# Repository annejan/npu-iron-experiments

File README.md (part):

# IRON experiments on a Ryzen AI NPU

One night (7 November 2026) of finding out what the NPU in an AMD Ryzen AI 7 PRO 350 laptop
(a ThinkPad; XDNA2, AMD codename Krackan Point, `xrt-smi` calls it "NPU Krackan") is good at,
programmed directly in IRON, the Python front end of AMD/Xilinx [mlir-aie](https://github.com/Xilinx/mlir-aie)
1.4.5, under Linux (openSUSE Tumbleweed, kernel 7.3 with the in-tree `amdxdna` driver). Demoscene
effects, physics simulations, audio DSP and one real object detector, each checked against numpy
and timed; plus the probes that measured the chip's ceilings, and every trap hit on the way.

Most of the code was written by [Claude Code](https://claude.com/claude-code) (Anthropic's agent)
working with Anne Jan Brouwer over one evening and night; every commit carries a `Co-Authored-By`
trailer saying so. All numbers are measurements on this one laptop, not AMD specifications, unless
a line says otherwise. See "Credits and licences" at the end for what is borrowed from whom.

Short version: the chip is 32 small vector cores with 64 KB each, fed by fast DMA. It shines on
anything branchless and MAC-shaped where every lane does the same work: stencils, convolutions,
FIR audio, int8 matrix multiplies, lookup tables. It is poor at gathers, trig, fp32 multiplies and
anything that needs a big table. A dispatch costs ~160 us before any work, so batch work per call.

## Setup

Hardware and kernel: a Ryzen AI 300 NPU (Strix Point, Krackan Point or Strix Halo; PCI `1022:17f0`),
Linux 6.14 or newer with the in-tree `amdxdna` driver (`CONFIG_DRM_ACCEL_AMDXDNA`) and the `amdnpu`
firmware (Tumbleweed: `kernel-default` + `kernel-firmware-platform`). `/dev/accel/accel0` is owned by
`root:render`, so add yourself to the `render` group. `lsmod | grep amdxdna` and `ls /lib/firmware/amdnpu`
tell you whether both are there.

XRT (AMD's runtime) is not in any distribution. This repo expects it unpacked, not installed, in
`../ryzenai` (nothing goes into `/opt`):

```
mkdir -p ../ryzenai/dl ../ryzenai/x && cd ../ryzenai
# into dl/: RAI_1.9_Linux_NPU_XRT.zip from AMD's "Ryzen AI Software 1.9, Linux" download page (AMD EULA), which holds
#   xrt_202620.2.26.89_24.04-amd64-{base,base-dev,npu}.deb and xrt_plugin.2.26.260102.59.release_24.04-amd64-amdxdna.deb,
# plus the two Ubuntu 24.04 packages the XRT binaries link against:
#   libboost-filesystem1.83.0_*.deb and libboost-program-options1.83.0_*.deb (packages.ubuntu.com)
for d in dl/*.deb; do dpkg-deb -x "$d" "x/$(basename "$d" .deb)"; done     # no dpkg? ar p X.deb data.tar.zst | tar -x --zstd
mkdir -p xrt boost
for p in x/xrt_*/opt/xilinx/xrt x/xrt_plugin*/opt/xilinx/xrt; do cp -a "$p/." xrt/; done
cp -a x/libboost*/usr boost/
```

`env.sh` points `XILINX_XRT`, `LD_LIBRARY_PATH` and `PYTHONPATH` (for `pyxrt`) at those two
directories. `pyxrt` is built for CPython 3.12 and the `mlir_aie` wheel is `cp312`, hence `python3.12`
in `setup.sh` (Tumbleweed: `zypper in python312`). Then, from this directory:

```
./setup.sh                      # clones mlir-aie v1.4.5 (no submodules), makes ironenv/ with mlir_aie 1.4.5,
                                # the pinned Peano (llvm-aie) compiler and the demo extras (~2 GB)
./env.sh xrt-smi examine        # the device: "NPU Krackan 1 | aie2p | 6x8"
```

## Quick start

```
./env.sh make -C mlir-aie/programming_examples/basic/vector_scalar_mul run_py   # smoke test, ends with PASS!
./env.sh python probe/plasma.py --window        # 1080p plasma in a pygame window
./env.sh python fun/mandel.py                   # Mandelbrot zoom in the terminal; --png out.png writes one frame
./env.sh python fun/lenia.py --window           # Lenia
./env.sh python fun/reverb.py --live            # microphone -> NPU convolution reverb -> headphones
```

Every command runs from this directory (the scripts find each other through `fun/` and `probe/`).
The first run of each design compiles its kernels (0.4-1.7 s, cached in `~/.npu/cache`,
`NPU_CACHE_HOME` overrides), and every `./env.sh` call runs `xrt-smi examine` once to find the device,
so starts take a moment. Run one NPU job at a time. `--window` needs pygame-ce; the audio demos need
soundfile and sounddevice, the live ones headphones.

## Pictures

| | | |
|---|---|---|
|  Lenia, 27x27 kernel |  Physarum network |  Schrodinger double slit |
|  Ising at Tc |  Lattice-Boltzmann vortex street |  Ripple tank |
|  SDF sphere tracer |  Smooth-min blobs |  Mandelbrot, 32 cores |
|  Abelian sandpile, 2^18 grains |  Gray-Scott coral |  YOLO26n, 150 fps, real weights |
|  Cyclic CA demons |  Greenberg-Hastings spirals |  1080p plasma, 0.34 ms/frame |
|  Corridor impulse response, 3-D FDTD |  Neural style transfer, 5 styles, 16.7 ms/frame |  The NPU learns MNIST, 50 ms/epoch |
|  Pong via a shortcut (see the section) | | |

(The YOLO and style pictures are COCO 2017 image 30: photo by julie, https://www.flickr.com/photos/roosterfarm/3573516590, CC BY 2.0, boxes added / restyled by the NPU.)

## Hardware (xrt-smi: "NPU Krackan 1", aie2p, 6x8)

| | |
|---|---|
| Compute cores | 32 (8 columns x rows 2..5), 1.76 GHz |
| Per core | 64 KB data memory (4 banks of 16 KB), 512-bit vector unit, 2 DMA in + 2 out |
| Mem tiles | 8 (row 1), 512 KB each |
| Shim tiles | 8 (row 0), 2 DMA channels each way, host DDR access |
| Vector lanes | 64 x int8, 32 x int16, 16 x int32, 32 x bf16 |
| Native math | int add/mul/mac/shift/cmp/select/shuffle, bf16 mul, `aie::inv`, `aie::invsqrt`, `aie::sqrt`, `aie::exp2`, `aie::tanh` (bf16) |
| Not native | float vector multiply (emulated via bf16, ~50 bundles/vector), scalar float mul/div, int32 divide, 64-bit multiply, sin/cos (use tables / polynomials), per-lane gather |

Sources: the name and the 6x8 array from `xrt-smi examine`; tile memories, DMA channels and lane
widths from the AIE-ML v2 (aie2p) architecture documentation and `mlir-aie/programming_guide/section-1`.
AMD does not publish the clock: ~1.76 GHz is what the II-1 loop in `probe/burn.py` implies, and
`probe/npu_top.py` reads the driver's H clock. "Native" means Peano compiles it to vector
instructions rather than a library call.

## Measured ceilings (2026-11-07, `probe/`)

All numbers: this one laptop, Linux, XRT 2.26, mlir-aie 1.4.5, default power mode, CPU idle unless
stated, min or median after a warm-up call, host wall clock from Python unless the row says NPU time.
"1080p" frames are 1920x1088 (32 cores x 34 rows) cropped to 1080.

| What | Number |
|---|---|
| Dispatch floor, host wall clock | ~155-180 us per call |
| Host <-> NPU DMA, all 8 columns, in and out at the same time | ~31 GB/s each way = 63 GB/s aggregate at 64 MB, 21 GB/s each way at 8 MB; a second shim channel per column or 64 KB objects change nothing (`probe/bw2.py`; `probe/bw.py` with one channel and 16 KB objects: 26 GB/s). ghost-intuit report 52-98 GB/s one way on a Strix Point under Windows |
| 1920x1088 RGBA frame out | ~0.31 ms |
| One core, int16 vector mul loop at II 1 | ~52 G elements/s (ideal 56) (`probe/burn.py`) |
| All 32 cores, same loop, wall clock incl. floor | ~850 G int16 ops/s |
| 1080p plasma, 32 cores, packed RGBA, bit-exact | 0.34 ms/frame (`probe/plasma.py`) |
| On-chip Game of Life, 32 cores | 27.8 Gcell/s vs numpy 1.5 (`fun/life_chip.py`) |
| Rotozoomer / tunnel 1080p, scalar texture gathers, 32 cores | ~1.1 ms/frame (`fun/rotozoom.py`) |
| SDF sphere tracer 1080p, bf16 MAC + fp32 accumulators, 32 cores | 48 steps 7.1 ms (141 fps), 64 steps 8.3 ms (120 fps), 96 steps 11.4 ms (88 fps) (`fun/sdf.py --steps N`) |
| Blobs 1080p, 4 spheres + floor smooth-min, 48 steps, 5 distance evals per step | 38 ms/frame, 26 fps (`fun/blob.py`) |
| Slime chemotaxis 320x256, bf16, world on chip, 15 steps/dispatch | 41k steps/s, 3.4 Gcell-steps/s (`fun/slime.py`) |
| Ripple tank 320x384, int16 Q12, world on chip, 5 steps/dispatch | 17k steps/s, 2.1 Gcell-steps/s (`fun/water.py`) |
| Convolution reverb, 65536 taps, 2048-sample blocks, stereo | 0.43 ms NPU per block per channel (43 ms of audio), 308 GMAC/s in the calls; 41x real time over the whole Python loop on a stereo file, bit-exact vs FFT (`fun/reverb.py`) |
| Lenia 512x512, 27x27 kernel (729 taps/cell), int16 Q15 | 0.65-0.84 ms/step, 1200-1500 steps/s, ~250 GMAC/s, conv exact to 6 LSB (`fun/lenia.py`) |
| DX7 FM synth, 512 voices x 6 operators, 256-sample blocks | 0.5 ms per block (5.3 ms of audio), 1.6 G operator-samples/s, bit-exact replica (`fun/dx7.py`) |
| NAM guitar amp (WaveNet, 13320 MAC/sample), 64-sample blocks, 16 cores per amp | 0.54 ms per block (1.33 ms of audio) for two amps at once, 65.9 dB SNR vs the float32 model with bf16 hi+lo pairs, 48 dB with single bf16 weights; live at 1.3 ms blocks, no underruns (`fun/nam_amp.py`) |
| Fast neural style transfer (Johnson TransformerNet, 1.68 M params, 13.8 GMAC per 320x240 frame), int8, 31 phases on 32 cores in one dispatch | **16.7 ms per frame on the NPU**, 18.6 ms (54 fps) for the whole Python call with upload and readback; 45-52 dB PSNR from a numpy emulation of the int8 design, which is 27-45 dB from the float32 model depending on the style (`fun/style_cam.py`) |
| MNIST training (784-256-10 MLP, bf16 matmuls, fp32 master weights resident in L1, model parallel over 32 cores), 937 minibatches of 64 per dispatch | **49.5 ms per epoch** on the NPU back to back (84 ms when the 200 MB stream was just rewritten; numpy fp32 on the CPU: 280 ms), 96.4% test accuracy after one epoch, 97.9% after five (numpy, same setup: 96.7 / 97.9); initialisation bit-exact, one SGD step within about 1% of a bf16 numpy replica (`fun/mnist_npu.py`) |
| Pong from pixels, REINFORCE with the MNIST trainer (28x28 input, 3 actions), 3008 moves per update | 5 ms of NPU time per update. 10% -> 59% of points won against a scripted opponent, but by copying the opponent's paddle (a shortcut); without it in view, 0.3 -> 0.5 returns per point before collapsing (`fun/pong_npu.py`) |
| Additive synth, 3072 partials, 1024-sample blocks | 0.38 ms per block (21 ms of audio: 56x real time for all 3072 partials) = 8 G partial-samples/s, amplitude drift-free, 0.03 Hz tuning (`fun/additive.py`) |
| Binaural, 32 sources x 2 ears x 160 taps, 1024-sample blocks | 0.28 ms per block (dispatch-bound), bit-exact, 38x real time (`fun/binaural.py`) |
| conv2d engine 512x512: K=3 / 7 / 15 | 0.27 / 0.35 / 0.91 ms per pass, 1-4 LSB vs numpy (`fun/conv2d.py`) |
| Physarum 120k agents + NPU blur | 13.8 ms/step total, NPU 0.7 ms of it (the agents are the cost) (`fun/physarum.py`) |
| Ising 512x512, 20 half-sweeps per dispatch | 2-3 G spin-updates/s (7-11k sweeps/s); |M| and E within 1% of Onsager at T = 1.5..3.5 (`fun/ising.py`) |
| YOLO26n (stock example), whole network on 32 tiles, batch 1 | **6.5 ms per 640x640 image = 150 fps** with the real XINT8 weights, 8/8 coco128 images bit-exact vs the integer oracle and ONNX Runtime, mAP50 0.97 on those 8. The same network measured 11.3 ms earlier, with seeded weights while the export saturated the CPU (see the CPU-load note) |
| 2-D Schrodinger 512x512, int32, 1 step/dispatch (R for 3 rows + I for 1 per output row) | 0.47 ms/step, 2100 steps/s; norm conserved to 0.3% over 1400 steps (`fun/schrodinger.py`) |
| Sandpile 512x512, 101 rounds/dispatch | 90k rounds/s (2^18 grains stable in 50k rounds = 0.6 s), grains conserved exactly (`fun/sandpile.py`) |
| Cyclic CA / Greenberg-Hastings 512x512, int16, 21 steps/dispatch | 45k / 39k steps/s = 12 / 10 Gcell-steps/s, bit-exact (`fun/spiral.py`) |
| Gray-Scott 512x256, 101 steps/dispatch | 4300 steps/s, 0.6 Gcell-steps/s (`fun/grayscott.py`) |
| 3-D wave FDTD 32x32x128 (131k cells), int32, 1 step/dispatch | 0.21 ms/step NPU, 0.26-0.31 ms incl. host readback: 1 s of 8 kHz room response in 2.5 s (`fun/room.py`) |
| LBM D2Q9 384x256, bf16 deviations, 1 step per dispatch (DMA-bound) | 2700 steps/s, 0.27 Gcell-steps/s (`fun/lbm.py`) |
| Mandelbrot 1080p, 400 iterations, Q24 int32, 16 lanes, 32 cores | 26.9 ms (numpy 5.4 s); the old scalar int64 kernel is 34x slower per core, both measured at 480x270 on 32 cores (`fun/mandel.py --bench`) |

Rule of thumb for effects: a dispatch costs ~160 us before any work, a full-HD frame
costs ~0.3 ms of DMA, and compute is almost free unless the kernel is scalar.
Batch work per dispatch; keep one call per frame.

## Demos (`fun/`)

| | |
|---|---|
| `mandel.py` | zoom in the terminal; `--bench`, `--png out.png`, `--scalar` for the old kernel |
| `life.py`, `life_chip.py`, `life_window.py` | Game of Life, host-halo and on-chip (snake of 32 cores) variants, pygame window |
| `rotozoom.py` | rotozoomer + tunnel, `--window` (TAB switches) |
| `sdf.py` | sphere-traced signed distance field (repeated spheres + floor), `--window`, `--check` for the static loop report |
| `blob.py` | four spheres + floor joined with smooth-min (the "bloep", Dutch for the plop of merging blobs), numeric normals, specular; reuses sdf.py's plumbing |
| `slime.py` | slime mould / ant trails as grid chemotaxis (density + pheromone, conservative upwind flux), on-chip world, `--window` (click = food) |
| `water.py` | ripple tank, int16 Q12 height field, on-chip world, `--window` (drag = drops, R = rain) |
| `reverb.py` | convolution reverb: 65536-tap IR (1.4 s), 2048 taps per core, int16 Q15, `sliding_mac` FIR; `in.wav` offline with numpy check, `--play` live through the speakers, `--live` microphone -> headphones (3% load) |
| `lenia.py` | Lenia continuous CA: 27x27 ring-kernel convolution per step via `sliding_mac`, DDR world streamed through the cores with a 27-row ring buffer in L1, bf16 growth; `--window` |
| `room.py` | 3-D FDTD room acoustics (32x32x128 cells, int32 Q28, 8 kHz), streams z-planes through the cores, records a stereo impulse response; `--check` vs numpy |
| `binaural.py` | 32 sources around the head, one per core, MIT KEMAR HRTFs (Gardner & Martin 1994, downloaded to `data/kemar/` on first run), two `sliding_mac` FIRs per core; writes `binaural_arpeggio.wav`, `--play` live |
| `conv2d.py` | generic K x K convolution engine over a DDR world (the Lenia machinery parameterised), self-test vs numpy |
| `physarum.py` | real slime-mould networks (Jones 2010 agents on the CPU, trail blur + decay on the NPU via conv2d) |
| `ising.py` | 2-D Ising, checkerboard Metropolis, xorshift32 RNG in the lanes, world on chip; |M| and E vs Onsager's exact solution; `--window` (up/down: temperature) |
| `yolo_cam.py` | YOLO26n object detection on the webcam or an image, via the stock `mlir-aie/programming_examples/ml/yolo26n`. Needs its exported weights: follow that example's README (`make export`, `make data` with `IRON_EXAMPLE_WEIGHTS_DIR` set; the Ultralytics checkpoint is AGPL and not in this repo; ~25 min of calibration). `--synthetic 7` runs without a checkpoint (timing real, boxes noise) |
| `schrodinger.py` | 2-D Schrodinger equation, Visscher scheme, int32 Q28, 5-row sliding window; a wave packet through a double slit; `--check` vs numpy |
| `sandpile.py` | Abelian sandpile, exact int16 stencil on chip, 2^18 grains (the default; 2^19 runs off the 512 grid) dropped in portions (abelian), the fractal in `sandpile.png` |
| `grayscott.py` | Gray-Scott reaction-diffusion, int16 Q14, world on chip; `--F --k` or live keys through Pearson's map |
| `water_resident.py` | the ripple tank with its world resident in L1 across dispatches (`Buffer` + `while_true` workers, one command object per call); measures the DDR saving and the autosuspend reset |
| `additive.py` | additive synthesiser: 3072 partials as magic-circle oscillators, 32 samples of each sinusoid in the lanes, one rotation per sub-block, no trig; bells and STFT resynthesis to wav, bit-exact numpy replica |
| `spiral.py` | integer excitable media on chip: cyclic CA (16 states, demons) and Greenberg-Hastings (8 states, spiral waves), bit-exact vs numpy |
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
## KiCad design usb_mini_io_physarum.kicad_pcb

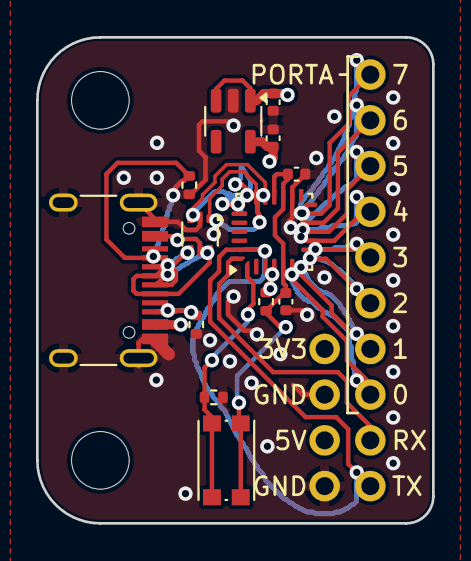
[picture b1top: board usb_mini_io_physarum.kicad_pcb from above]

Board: 2 copper layers, 22.0 x 27.0 mm, 16 parts (1 on the bottom side), 23 nets.

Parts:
C1, C2, C3, C4: 1uF; C_0402_1005Metric
J1: USB_C_Receptacle_USB2.0; USB_C_Receptacle_HRO_TYPE-C-31-M-12
J2: Conn_01x04_Pin; PowerHeader
J38: Conn_01x10_Pin; STM32IOHeader
J39: SWDHeader_covered
R1, R2, R3, R8: 5.1k; R_0402_1005Metric
SW1: SW_SPST; SW_Push_1P1T_NO_CK_KMR2
U1: STM32F042G6Ux; QFN-28_4x4mm_P0.5mm
U2: AP2112K-3.3; SOT-23-5
U3: USBLC6-2P6; SOT-666

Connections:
3V3: C2.1, C3.1, C4.1, J2.1, R8.1, SW1.1 (A), U1.5 (VDDA), U1.17 (VDD), U1.18 (VDDIO2), U2.5 (VOUT)
A0: J38.8, U1.6 (PA0)
A1: J38.7, U1.7 (PA1)
A2: J38.6, U1.8 (PA2)
A3: J38.5, U1.9 (PA3)
A4: J38.4, U1.10 (PA4)
A5: J38.3, U1.11 (PA5)
A6: J38.2, U1.12 (PA6)
A7: J38.1, U1.13 (PA7)
D+: U1.20 (PA10/PA12), U3.1 (I/O1)
D-: U1.19 (PA9/PA11), U3.3 (I/O2)
GND: C1.2, C2.2, C3.2, C4.2, J1.A1 (GND), J1.A12 (GND), J1.B1 (GND), J1.B12 (GND), J1.S1 (SHIELD), J2.2, J2.4, J39.SWDGND, R1.1, R2.1, R3.2, U1.16 (VSSA), U2.2 (GND), U3.2 (GND)
unnamed: J1.A5 (CC1), R1.2
unnamed: J1.B5 (CC2), R2.2
unnamed: J1.A6 (D+), J1.B6 (D+), U3.6 (I/O1)
unnamed: J1.A7 (D-), J1.B7 (D-), U3.4 (I/O2)
unnamed: R3.1, SW1.2 (B), U1.1 (PB8)
unnamed: R8.2, U1.4 (NRST)
RX: J38.9, U1.28 (PB7)
SWDCLK: J39.SWDCLK, U1.22 (PA14)
SWDIO: J39.SWDIO, U1.21 (PA13)
TX: J38.10, U1.27 (PB6)
VCC: C1.1, J1.A4 (VBUS), J1.A9 (VBUS), J1.B4 (VBUS), J1.B9 (VBUS), J2.3, U2.1 (VIN), U2.3 (EN), U3.5 (VBUS)

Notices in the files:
README.md:
Credits and licences:
The code in this repository is MIT (`LICENSE`), Copyright 2026 Anne Jan Brouwer. It was written
with Claude Code; the commit trailers name the agent.
The repository follows the [REUSE](https://reuse.software) specification: `REUSE.toml` gives the copyright and
licence of every file that is not MIT, the licence texts are in `LICENSES/`, and CI runs `reuse lint` on every
push (`.github/workflows/reuse.yml`). Run it locally with `reuse lint`.
One exception: the `Detector` class in `fun/yolo_cam.py` is adapted from the mlir-aie example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
are theirs, CC BY 4.0.
